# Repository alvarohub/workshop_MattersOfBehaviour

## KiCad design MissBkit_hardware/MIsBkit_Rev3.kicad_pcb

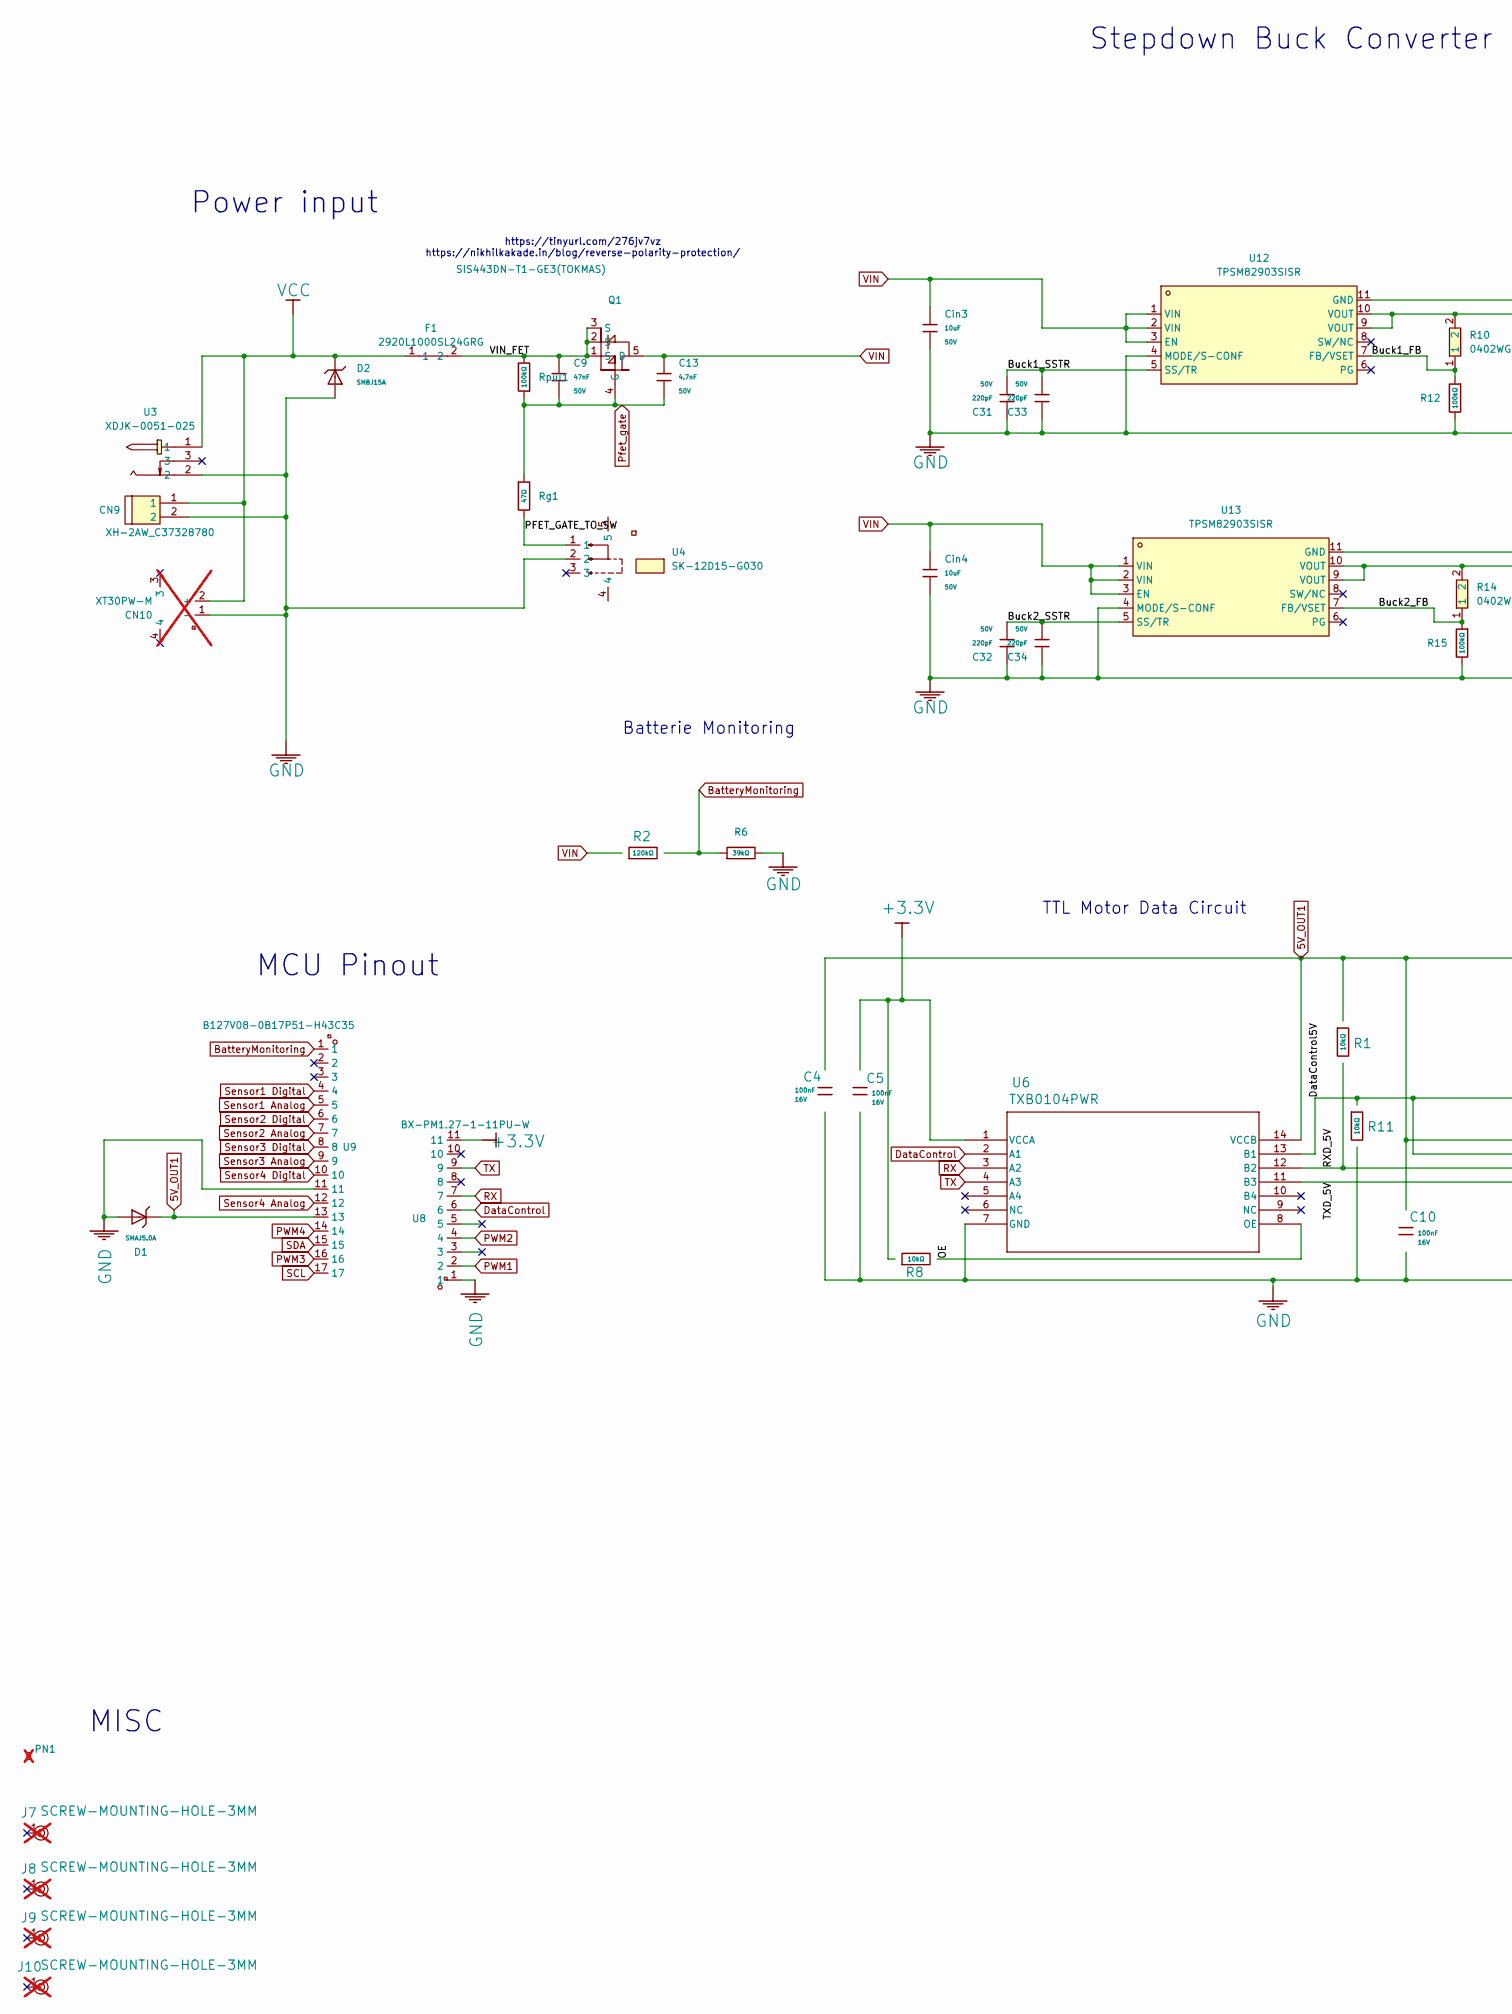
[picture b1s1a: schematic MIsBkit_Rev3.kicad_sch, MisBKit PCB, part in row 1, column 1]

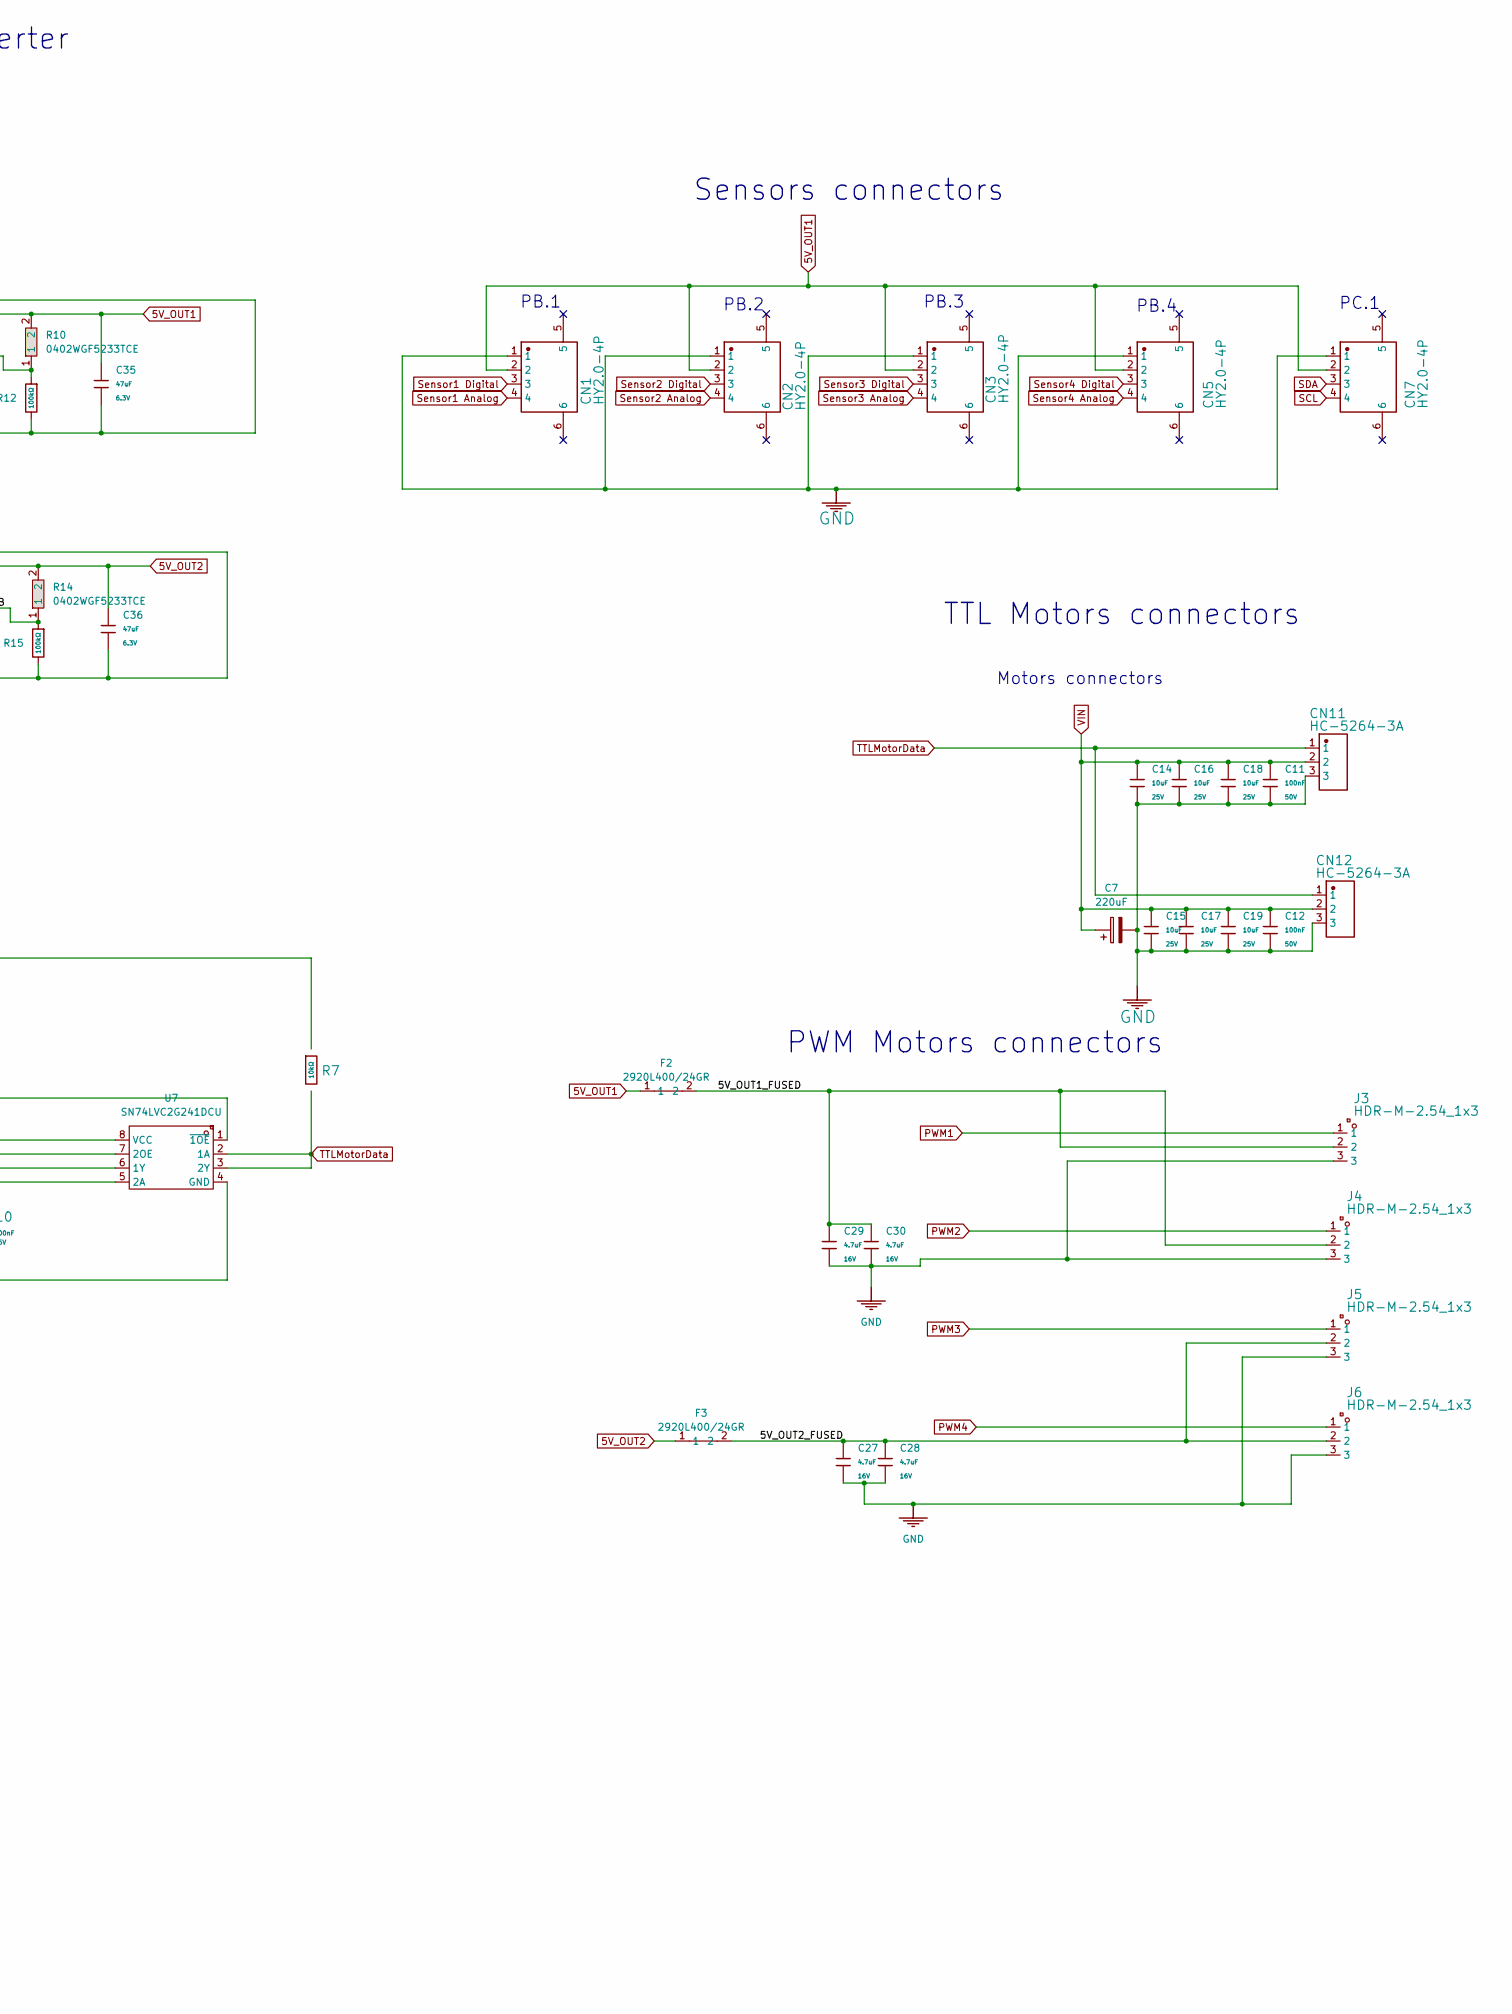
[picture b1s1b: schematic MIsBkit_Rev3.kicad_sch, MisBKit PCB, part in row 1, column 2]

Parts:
C4, C5, C10: 100nF; C_0402; Voltage Rated 16V; Tolerance ±10%; Part CL05B104KO5NNNC; LCSC C1525
C7: 220uF; CAP-SMD_BD6.3-L6.6-W6.6-FD; LCSC Part C7471881
C9: 47nF; C_0603; Voltage Rated 50V; Tolerance ±10%; Part CL10B473KB8NNNC; LCSC C1622
C11, C12: 100nF; C_0603; Voltage Rated 50V; Tolerance ±10%; Part CC0603KRX7R9BB104; LCSC C14663
C13: 4.7nF; C_0402; Voltage Rated 50V; Tolerance ±10%; Part 0402B472K500NT; LCSC C1538
C14, C15, C16, C17, C18, C19: 10uF; C_0603; Voltage Rated 25V; Tolerance ±20%; Part CL10A106MA8NRNC; LCSC C96446
C27, C28, C29, C30: 4.7uF; C_0603; Voltage Rated 16V; Tolerance ±10%; Part CL10A475KO8NNNC; LCSC C19666
C31, C32, C33, C34: 220pF; C_0402; Voltage Rated 50V; Tolerance ±10%; Part 0402B221K500NT; LCSC C1530
C35, C36: 47uF; C_0805; Voltage Rated 6.3V; Tolerance ±20%; Part CL21A476MQYNNNE; LCSC C16780
CN1, CN2, CN3, CN5, CN7: HY2.0-4P; CONN-SMD_4P-P2.00_HY2.0-4P; Manufacturer Part HY-4P立贴; LCSC C52037433
CN9: XH-2AW_C37328780; CONN-TH_2P-P2.50_XH-2AW; LCSC Part C33132
CN10: XT30PW-M; CONN-TH_XT30PW-M; LCSC Part C431092; not fitted
CN11, CN12: HC-5264-3A; Molex_SPOX_5267-03A_1x03_P2.50mm_Vertical; Manufacturer Part HC-5264-3A; LCSC C2845815
Cin3, Cin4: 10uF; C_1206; Voltage Rated 50V; Tolerance ±10%; Part CL31A106KBHNNNE; LCSC C13585
D1: SMAJ5.0A; D_SMA; Breakdown Voltage 6.4V; Part SMAJ5.0A; LCSC C2925443
D2: SMBJ15A; D_SMB; Part SMBJ15A; LCSC C19077569
F1: 2920L1000SL24GRG; F2920; LCSC Part C47345590
F2, F3: 2920L400/24GR; F1210; LCSC Part C22379950
J3, J4, J5, J6: HDR-M-2.54_1x3; CONN-TH_HX-PZ2.54-1X3P-ZZ; LCSC Part C32713269
J7, J8, J9, J10: SCREW-MOUNTING-HOLE-3MM; Hole, 3mm; not fitted
PN1: Part_Num_JLCPCB; not fitted
Q1: SIS443DN-T1-GE3(TOKMAS); PDFN3333-8_L3.1-W3.2-P0.65-LS3.4-BL_1; LCSC Part C48586476
R1, R7, R8, R11: 10kΩ; R_0402; Overload Voltage (Max) 50V; Tolerance ±1%; Part 0402WGF1002TCE; LCSC C25744
R2: 120kΩ; R_0402; Overload Voltage (Max) 50V; Tolerance ±1%; Part 0402WGF1203TCE; LCSC C25750
R6: 39kΩ; R_0402; Overload Voltage (Max) 50V; Tolerance ±1%; Part 0402WGF3902TCE; LCSC C25783
R10, R14: 0402WGF5233TCE; R_0402; LCSC Part C27011
R12, R15: 100kΩ; R_0402; Overload Voltage (Max) 50V; Tolerance ±1%; Part 0402WGF1003TCE; LCSC C25741
Rg1: 47Ω; R_0402; Overload Voltage (Max) 50V; Tolerance ±1%; Part 0402WGF470JTCE; LCSC C25118
Rpul1: 100kΩ; R_0603; Overload Voltage (Max) 75V; Tolerance ±1%; Part 0603WAF1003T5E; LCSC C25803
U3: XDJK-0051-025; DC-IN-TH_XDJK-0051-025; LCSC Part C7498153
U4: SK-12D15-G030; SW-SMD_3P-L8.6-W4.5_SK-12D15-G030; LCSC Part C7544904
U6: TXB0104PWR; TSSOP-14_4.4x5mm_P0.65mm; LCSC C60708
U7: SN74LVC2G241DCU; VSSOP-8_L2.3-W2.0-P0.50-LS3.1-BR; LCSC Part C10430
U8: BX-PM1.27-1-11PU-W; HDR-SMD_11P-P1.27-V-F-LS3.5; LCSC Part C41366880
U9: B127V08-0B17P51-H43C35; HDR-SMD_17P-P1.27-V-F-LS3.5; LCSC Part C41427152
U12, U13: TPSM82903SISR; USIP-11_L3.0-W2.8_TPSM82901SISR; LCSC Part C6290583

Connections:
5V_OUT1: C4.1, C10.1, C35.1, CN1.2, CN2.2, CN3.2, CN5.2, CN7.2, D1.1, F2.1, R1.1, R7.1, R10.2, U6.14 (VCCB), U7.8 (VCC), U9.13, U12.9 (VOUT), U12.10 (VOUT)
5V_OUT2: C36.1, F3.1, R14.2, U13.9 (VOUT), U13.10 (VOUT)
+3.3V: C5.1, R8.1, U6.1 (VCCA), U8.11
/5V_OUT1_FUSED: C29.1, C30.1, F2.2, J3.2, J4.2
/5V_OUT2_FUSED: C27.1, C28.1, F3.2, J5.2, J6.2
/Buck1_FB: R10.1, R12.1, U12.7 (FB/VSET)
/Buck1_SSTR: C31.2, C33.2, U12.5 (SS/TR)
/Buck2_FB: R14.1, R15.1, U13.7 (FB/VSET)
/Buck2_SSTR: C32.2, C34.2, U13.5 (SS/TR)
/DataControl5V: R11.1, U6.13 (B1), U7.1 (~1OE), U7.7 (2OE)
/OE: R8.2, U6.8 (OE)
/PFET_GATE_TO_SW: Rg1.2, U4.1
/RXD_5V: R1.2, U6.12 (B2), U7.6 (1Y)
/TXD_5V: U6.11 (B3), U7.5 (2A)
/VIN_FET: C9.1, F1.2, Q1.1 (S), Q1.2 (S), Q1.3 (S), Rpul1.2
BatteryMonitoring: R2.2, R6.1, U9.1
DataControl: U6.2 (A1), U8.6
GND: C4.2, C5.2, C7.2, C10.2, C11.2, C12.2, C14.2, C15.2, C16.2, C17.2, C18.2, C19.2, C27.2, C28.2, C29.2, C30.2, C31.1, C32.1, C33.1, C34.1, C35.2, C36.2, CN1.1, CN2.1, CN3.1, CN5.1, CN7.1, CN9.2, CN10.1 (-), CN11.3, CN12.3, Cin3.2, Cin4.2, D1.2, D2.2, J3.3, J4.3, J5.3, J6.3, R6.2, R11.2, R12.2, R15.2, U3.2, U4.2, U6.7 (GND), U7.4 (GND), U8.1, U9.11, U12.4 (MODE/S-CONF), U12.11 (GND), U13.4 (MODE/S-CONF), U13.11 (GND)
PWM1: J3.1, U8.2
PWM2: J4.1, U8.4
PWM3: J5.1, U9.16
PWM4: J6.1, U9.14
Pfet_gate: C9.2, C13.2, Q1.4 (G), Rg1.1, Rpul1.1
RX: U6.3 (A2), U8.7
SCL: CN7.4, U9.17
SDA: CN7.3, U9.15
Sensor1 Analog: CN1.4, U9.5
Sensor1 Digital: CN1.3, U9.4
Sensor2 Analog: CN2.4, U9.7
Sensor2 Digital: CN2.3, U9.6
Sensor3 Analog: CN3.4, U9.9
Sensor3 Digital: CN3.3, U9.8
Sensor4 Analog: CN5.4, U9.12
Sensor4 Digital: CN5.3, U9.10
TTLMotorData: CN11.1, CN12.1, R7.2, U7.2 (1A), U7.3 (2Y)
TX: U6.4 (A3), U8.9
VCC: CN9.1, CN10.2 (+), D2.1, F1.1, U3.1
VIN: C7.1, C11.1, C12.1, C13.1, C14.1, C15.1, C16.1, C17.1, C18.1, C19.1, CN11.2, CN12.2, Cin3.1, Cin4.1, Q1.5 (D), R2.1, U12.1 (VIN), U12.2 (VIN), U12.3 (EN), U13.1 (VIN), U13.2 (VIN), U13.3 (EN)

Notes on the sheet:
MISC
MCU Pinout
PC.1
https://tinyurl.com/276jv7vz https://nikhilkakade.in/blog/reverse-polarity-protection/
PB.3
TTL Motors connectors
Batterie Monitoring
PWM Motors connectors
Stepdown Buck Converter
PB.2
PB.1
PB.4
TTL Motor Data Circuit
Power input
Motors connectors
Sensors connectors

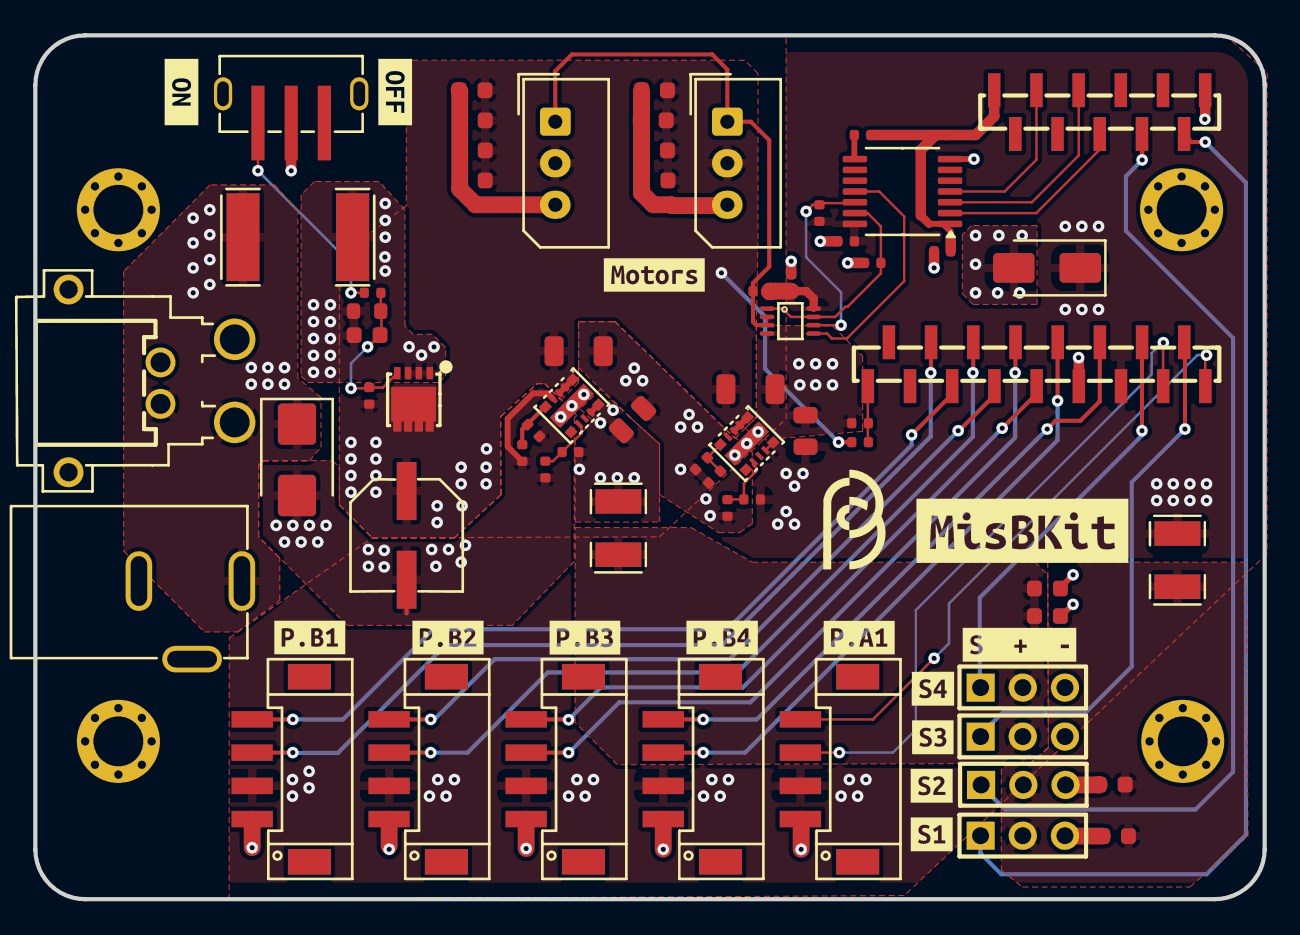
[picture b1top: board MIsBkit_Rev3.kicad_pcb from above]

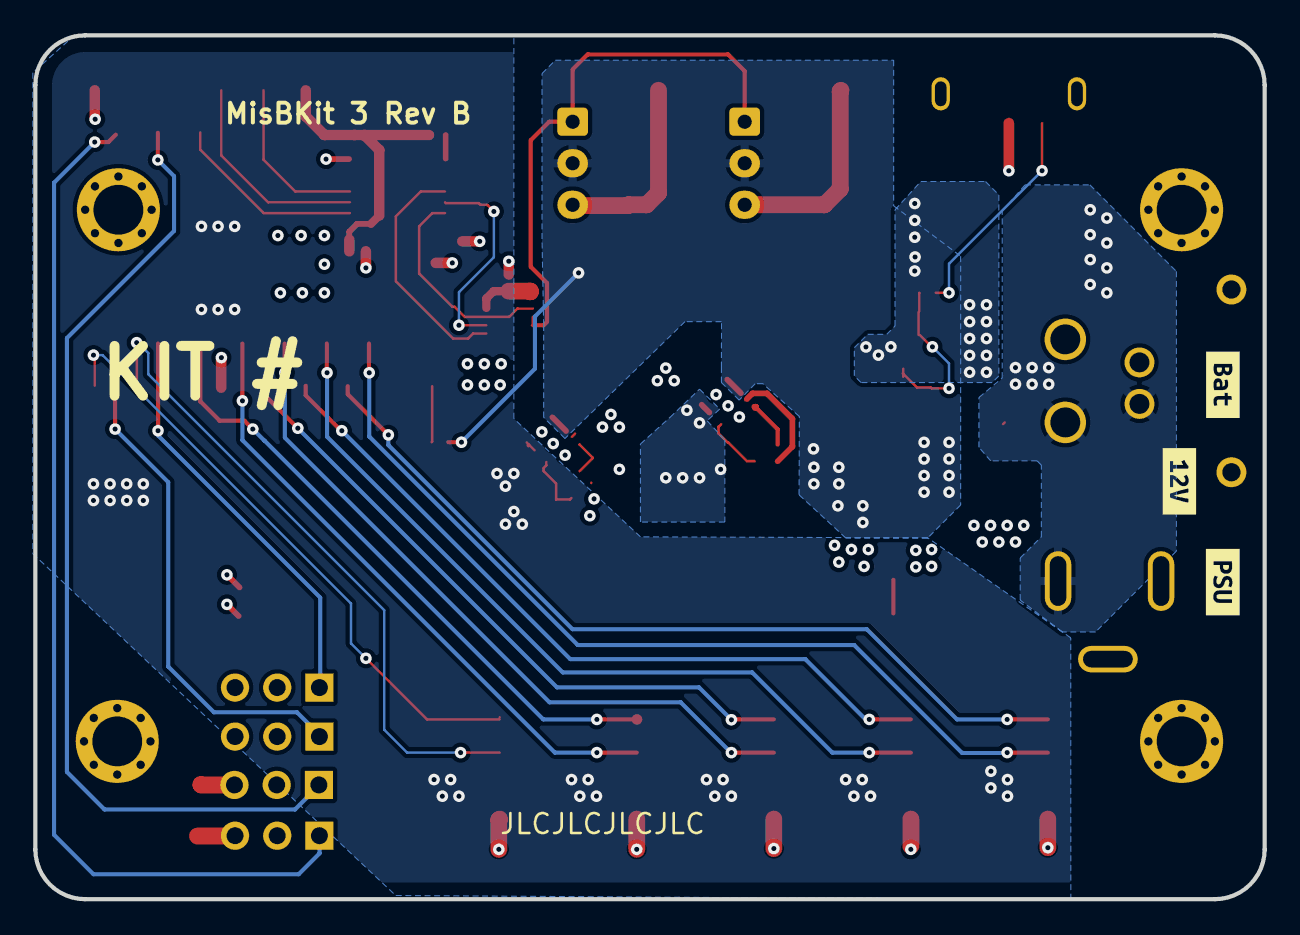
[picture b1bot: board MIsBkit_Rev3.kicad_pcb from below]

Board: 4 copper layers, 74.0 x 52.0 mm, 87 parts (3 on the bottom side), 38 nets.

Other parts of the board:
kibuzzard-69B192BF: G***; kibuzzard-69B192BF
kibuzzard-69B19130: G***; kibuzzard-69B19130
kibuzzard-69B19139: G***; kibuzzard-69B19139
kibuzzard-69B19140: G***; kibuzzard-69B19140
kibuzzard-69B19147: G***; kibuzzard-69B19147
kibuzzard-69B19182: G***; kibuzzard-69B19182
kibuzzard-697CF500: G***; kibuzzard-697CF500
kibuzzard-6924EAAF: G***; kibuzzard-6924EAAF
kibuzzard-6924EAC7: G***; kibuzzard-6924EAC7
kibuzzard-6924EB42: G***; kibuzzard-6924EB42
kibuzzard-6924EB61: G***; kibuzzard-6924EB61
kibuzzard-6924EB76: G***; kibuzzard-6924EB76
kibuzzard-6924EB83: G***; kibuzzard-6924EB83
kibuzzard-6924ECE6: G***; kibuzzard-6924ECE6
kibuzzard-6924ECF3: G***; kibuzzard-6924ECF3
kibuzzard-6924ECFF: G***; kibuzzard-6924ECFF
kibuzzard-69828209: G***; kibuzzard-69828209
